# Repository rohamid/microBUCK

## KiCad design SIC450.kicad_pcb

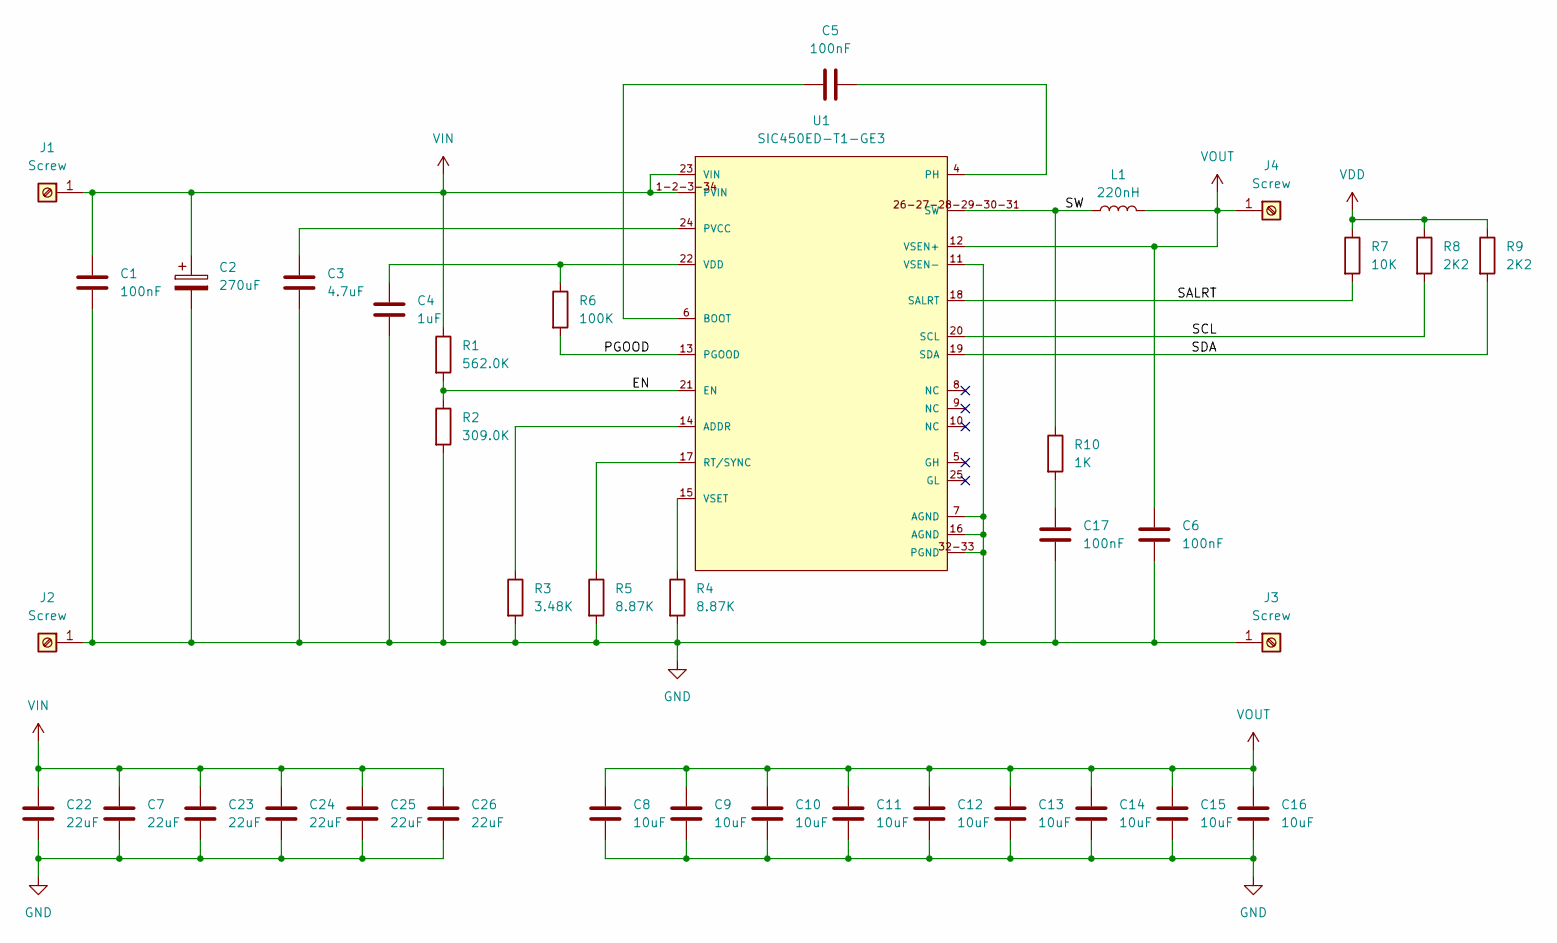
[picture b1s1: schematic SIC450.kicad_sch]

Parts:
C1, C5, C6: 100nF; C_0402_1005Metric
C2: 270uF; CP_Elec_6.3x4.9
C3: 4.7uF; C_0603_1608Metric
C4: 1uF; C_0603_1608Metric
C7, C22, C23, C24, C25, C26: 22uF; C_1210_3225Metric
C8, C9, C10, C11, C12, C13, C14, C15, C16: 10uF; C_1210_3225Metric
C17: 100nF; C_0805_2012Metric
J1, J2, J3, J4: Screw; square_terminal
L1: 220nH; Vishay-IHLP-5050FD-FP_2.945x4.95-3D_6.4-0-0-MFG
R1: 562.0K; R_0402_1005Metric
R2: 309.0K; R_0402_1005Metric
R3: 3.48K; R_0402_1005Metric
R4, R5: 8.87K; R_0402_1005Metric
R6: 100K; R_0402_1005Metric
R7: 10K; R_0402_1005Metric
R8, R9: 2K2; R_0402_1005Metric
R10: 1K; R_1206_3216Metric
U1: SIC450ED-T1-GE3; Vishay-T18-0377-08_2018-A-MFG; output voltage 0.3-12V; mouser part number 78-SIC450ED-T1-GE3; digikey description 4.5 V TO 20 V INPUT, 15 A, 25 A,

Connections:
/EN: R1.2, R2.1, U1.21 (EN)
/PGOOD: R6.2, U1.13 (PGOOD)
/SALRT: R7.2, U1.18 (SALRT)
/SCL: R8.2, U1.20 (SCL)
/SDA: R9.2, U1.19 (SDA)
/SW: L1.1, R10.1, U1.26-27-28-29-30-31 (SW)
GND: C1.2, C2.2, C3.2, C4.2, C6.2, C7.2, C8.2, C9.2, C10.2, C11.2, C12.2, C13.2, C14.2, C15.2, C16.2, C17.2, C22.2, C23.2, C24.2, C25.2, C26.2, J2.1, J3.1, R2.2, R3.2, R4.2, R5.2, U1.7 (AGND), U1.11 (VSEN-), U1.16 (AGND), U1.32-33 (PGND)
unnamed: C17.1, R10.2
unnamed: R3.1, U1.14 (ADDR)
unnamed: C5.1, U1.6 (BOOT)
unnamed: C5.2, U1.4 (PH)
unnamed: C3.1, U1.24 (PVCC)
unnamed: R5.1, U1.17 (RT/SYNC)
unnamed: C4.1, R6.1, U1.22 (VDD)
unnamed: R4.1, U1.15 (VSET)
VDD: R7.1, R8.1, R9.1
VIN: C1.1, C2.1, C7.1, C22.1, C23.1, C24.1, C25.1, C26.1, J1.1, R1.1, U1.1-2-3-34 (PVIN), U1.23 (VIN)
VOUT: C6.1, C8.1, C9.1, C10.1, C11.1, C12.1, C13.1, C14.1, C15.1, C16.1, J4.1, L1.2, U1.12 (VSEN+)

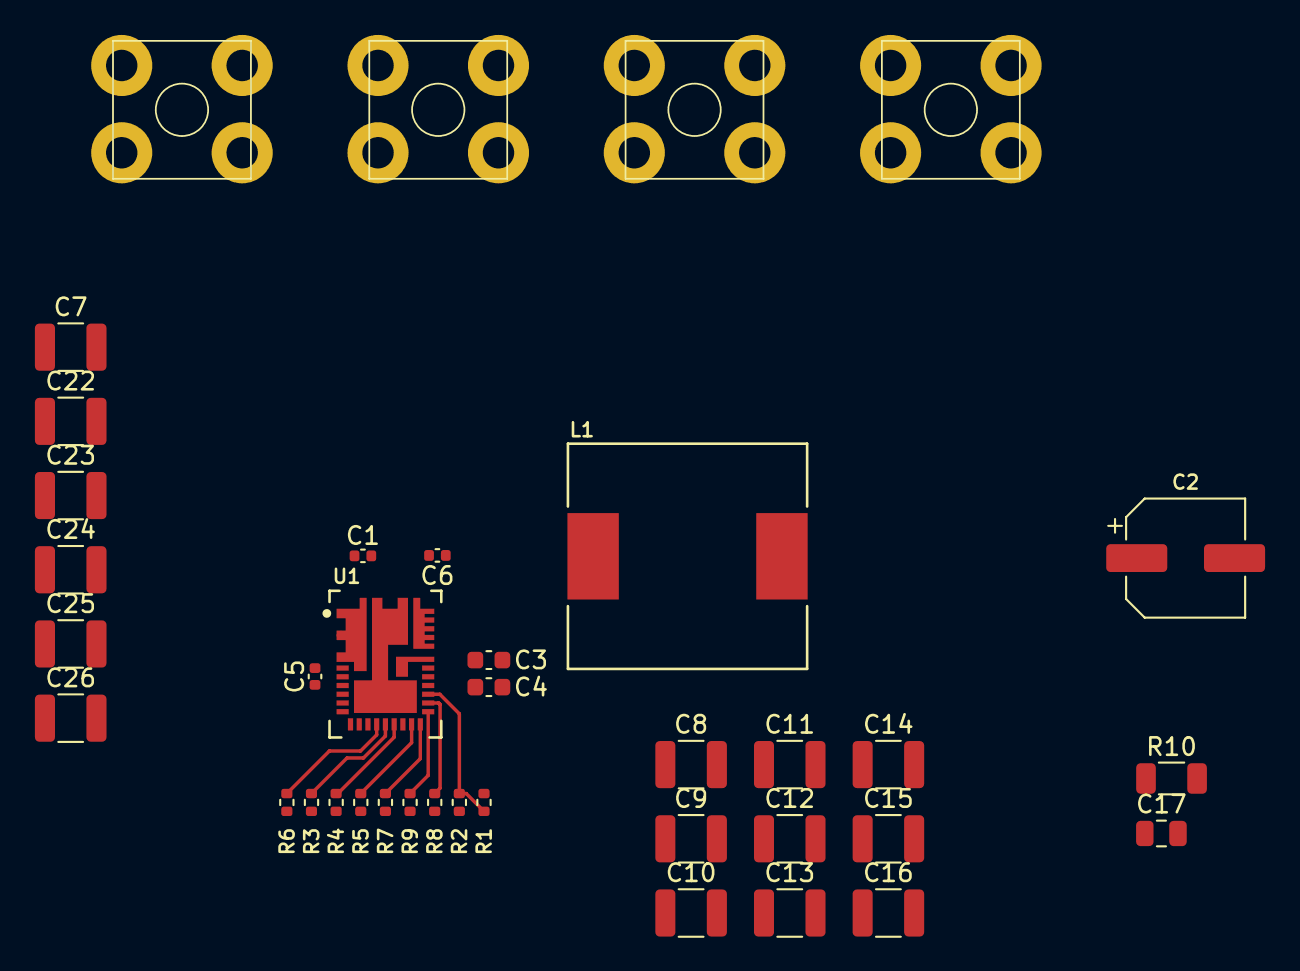
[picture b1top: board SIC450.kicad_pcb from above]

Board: 2 copper layers, 38 parts (0 on the bottom side), 18 nets.
